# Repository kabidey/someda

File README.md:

# someda

**Describe a circuit. Get a KiCad project you could send to a board house, with every claim checked.**

someda is an electronics design engine written in Rust. You give it a small description of a
circuit: the parts, how they connect, and a bit of intent such as "put the USB connector on
the top edge". It produces a KiCad schematic and board, placed and routed, checked for signal
integrity, stability and heat, verified by KiCad's own rule checks, and exported as Gerbers,
drill files, a bill of materials, a JLCPCB order package and 3D renders.

It never tells you a board is done unless six independent checks agree. When something is
wrong, it tells you what, in plain words, instead of hiding it.

The description can come from you, from a script, or from a language model. The model only
writes intent. The engine owns every coordinate, every trace and every verdict. If a plan has
a problem the engine can fix on its own (a misspelled footprint, a missing decoupling
capacitor), it fixes it and builds again.

MIT license. Made by [SomTronics](https://somtronics.org).

## Two ways to use it

**The desktop app.** `someda-app` is a window. Double-click it and it guides you from "which
language model" to "here are your Gerbers". This is the easiest way in. See
[The desktop app](#the-desktop-app) below.

**The command line.** `someda` is the engine itself. Write a plan file, run one command, read
the result. Scripts, CI pipelines and other programs use this. See [Quick start](#quick-start).

Both come in every release archive.

## What happens in a build

```
plan -> schematic -> footprints -> placement -> routing -> audits -> KiCad checks -> exports -> six gates
```

1. **Schematic.** A readable sheet with real library symbols and labelled pins. KiCad's ERC
   checks it.
2. **Footprints.** Real KiCad library footprints, found by their library name. A misspelled
   name is replaced by the closest footprint in that library, and the engine says so. A part
   the libraries do not have is reported, never guessed.
3. **Placement.** Mounting holes go in their corners. Edge connectors are turned so their
   opening faces the edge, then placed on it. Parts sit next to the pins they share a net
   with. Fine-pitch chips get room for their escape vias. Hot parts keep their distance.
   A connector that finds no room on its edge is moved to the next edge and the board is
   placed again.
4. **Routing.** Two, four or six copper layers on JLCPCB rules. Copper planes on the inner
   layers, with a via for every pad that needs them. Escape vias for every fine-pitch pin.
   Differential pairs are routed first, as coupled pairs at a real cross-section from the
   fab's impedance tables, with matched lengths. Fast nets keep 3W/5W spacing from each
   other. Impedance-controlled traces get the width the stackup calls for and stay over a
   solid plane. When something does not fit, the router rips up and tries again.
5. **Audits on the routed copper.** Stray inductance and capacitance per net. Standing-wave
   ratio and stub resonances. Unterminated transmission lines. Crosstalk measured on the
   actual copper. The loop inductance of every decoupling capacitor as mounted. Regulator
   output capacitance against the datasheet. Crystal loads and trace lengths. Switch-node
   loops. Power delivery impedance per rail. Junction temperatures. Whether JLCPCB can make
   it at all.
6. **KiCad.** ERC, DRC with the zones refilled, Gerbers, drill files and map, position file,
   bill of materials, 3D renders with component bodies.
7. **Exports.** A detailed BOM (quantity, references, value, part number, LCSC number,
   package) and a JLCPCB order package: Gerber zip with Protel names, merged drill file,
   assembly BOM, and a placement file with the rotation corrections JLCPCB expects.
8. **Six gates.** DRC, shorts, unrouted connections, copper pours, Gerbers, drill. All six
   pass and the build says `HONEST-DONE`. Anything else is `NOT DONE`, with the failing gate
   named.

If the plan had something the engine could repair, it repairs it and runs again, up to three
times by default. Each change is printed as a `repair:` line. Anything only you can change
is printed as a `suggest:` line with the exact edit. The plan as it was finally built is
saved next to the outputs as `plan.built.json`.

## The desktop app

Start `someda-app`. It takes you through six screens.

**Language model.** Pick a provider: Anthropic, OpenAI, DeepSeek, Kimi, Mistral, Z.ai,
Ollama Cloud, OpenRouter, NVIDIA NIM, an Ollama running on your own machine, or any other
endpoint that speaks the OpenAI protocol. Paste a key, ask the provider for its model list,
send one test message to be sure it works. The key is saved in your user configuration
folder where only you can read it, and it is handed to the engine through the environment,
never on a command line and never in a log.

**KiCad and libraries.** The app looks for `kicad-cli` and KiCad's footprint, symbol and
3D model libraries. If they are missing it can install KiCad for you: with apt on Debian
and Ubuntu, with the official installer on Windows, from the disk image on macOS.

**What to build.** Say what the board is for, what powers it, what it connects to. The
model may only do two things: ask you a few multiple-choice questions, each with a
recommended answer, about things that change the design; or propose a plan. It does not get
to ask about pinouts, and it does not get to declare the plan finished. The engine does
that. It checks every part against the installed KiCad libraries: does the symbol exist,
does the footprint exist, is every pin number the plan uses really a pin of that symbol.
It shows you the pin table it found, for example `U1: 1 GND, 2 TRIG, 3 OUT, 7 DISCH, 8 VCC`.
A misspelled name is corrected on the spot. When there is a real choice, you get a question
with the real options. When the model used a pin that does not exist, the plan goes back to
the model together with the pin table, and the model tries again. Nothing is built until the
engine is satisfied.

**Build.** Footprints and 3D models the libraries lack are fetched from KiCad's own
repositories. Then the engine runs exactly as it does on the command line, and you watch its
log.

**Result.** The six gates, the 3D render, what the engine repaired, what it suggests, and
the warnings it wants you to read. Buttons open the project folder, the board in KiCad and
the JLCPCB package.

**Change the design.** Describe the change in a sentence. The model proposes a revised plan.
You see the difference, line by line, and confirm. The engine builds the next version. Every
version keeps its plan, its outputs and its build log, so nothing is ever lost.

What has been verified: the whole flow on Linux under a virtual display with the 555
quick-start circuit, against an OpenAI-compatible server, through two versions, all six gates
both times. The Anthropic connection follows the published Messages API but was not tried
against the live service in that environment. The Windows and macOS binaries are built by the
same release workflow; their KiCad install flows have not yet been run on those systems.

## Install

Download the archive for your platform from the
[releases page](https://github.com/kabidey/someda/releases). Each one holds `someda` (the
command line) and `someda-app` (the window). Linux x86_64, macOS on Apple silicon and Intel,
and Windows x86_64 are covered.

To build from source you need stable Rust:

```bash
cargo build --release                                    # the command line, three direct dependencies
cargo build --release --features app --bin someda-app    # the window
```

For the verification and export steps you need [KiCad](https://www.kicad.org/) with
`kicad-cli` on your PATH, along with KiCad's footprint and 3D model libraries. Everything was
developed and verified against KiCad 10.0.6. If `kicad-cli` lives somewhere unusual, point
`SOMEDA_KICAD_CLI` at it. Without KiCad the engine still plans, places, routes and audits; it
simply reports the KiCad steps as skipped.

Using [Claude Code](https://claude.com/claude-code)? The
[someda plugin](https://github.com/kabidey/someda-claude-plugin) writes the plan from a
conversation, fetches missing parts, runs this engine and reports the gates.

## Quick start

`examples/plan_555.json` describes an NE555 blinking an LED, with 5 V arriving on a header at
the left edge and the timer's decoupling capacitor asked to sit next to it:

```json
{
  "name": "555 LED blinker",
  "description": "NE555 astable at about 1 Hz driving an LED",
  "layers": 2,
  "components": [
    {"reference": "U1", "value": "NE555", "lib_id": "Timer:NE555", "footprint": "Package_DIP:DIP-8_W7.62mm", "position": "center"},
    {"reference": "R1", "value": "10k",   "lib_id": "Device:R",   "footprint": "Resistor_SMD:R_0603_1608Metric"},
    {"reference": "R2", "value": "100k",  "lib_id": "Device:R",   "footprint": "Resistor_SMD:R_0603_1608Metric"},
    {"reference": "R3", "value": "330",   "lib_id": "Device:R",   "footprint": "Resistor_SMD:R_0603_1608Metric"},
    {"reference": "C1", "value": "4.7uF", "lib_id": "Device:C",   "footprint": "Capacitor_SMD:C_0805_2012Metric"},
    {"reference": "C2", "value": "100nF", "lib_id": "Device:C",   "footprint": "Capacitor_SMD:C_0603_1608Metric", "near": "U1"},
    {"reference": "D1", "value": "red",   "lib_id": "Device:LED", "footprint": "LED_SMD:LED_0805_2012Metric"},
    {"reference": "J1", "value": "5V in", "lib_id": "Connector:Conn_01x02", "footprint": "Connector_PinHeader_2.54mm:PinHeader_1x02_P2.54mm_Vertical", "position": "left_edge"}
  ],
  "nets": [
    {"name": "VCC", "pins": ["J1:1", "U1:8", "U1:4", "R1:1", "C2:1"]},
    {"name": "GND", "pins": ["J1:2", "U1:1", "C1:2", "C2:2", "D1:1"]},
    {"name": "DIS", "pins": ["U1:7", "R1:2", "R2:1"]},
    {"name": "THR", "pins": ["U1:6", "U1:2", "R2:2", "C1:1"]},
    {"name": "OUT", "pins": ["U1:3", "R3:1"]},
    {"name": "LED", "pins": ["R3:2", "D1:2"]}
  ]
}
```

Build it:

```bash
SOMEDA_PLAN_FILE=examples/plan_555.json SOMEDA_PROJECT_DIR=out someda ai build "555 LED blinker"
```

The engine prints every stage and finishes with the gate table. With someda 0.8.0 and
kicad-cli 10.0.6 this plan places 8 parts on a 43 by 35 mm board, routes all 15
connections, passes KiCad's ERC and DRC with no errors, and clears all six gates. Afterwards
`out/` contains:

```
out/circuit.kicad_sch  circuit.kicad_pcb  circuit.kicad_pro   the KiCad project
out/circuit-erc.rpt    circuit-drc.rpt                         KiCad's reports
out/fab/               Gerbers, drill and map, positions.csv, bom.csv, bom-detailed.csv, bom.md
out/fab/jlcpcb/        jlcpcb-gerbers.zip, jlcpcb-bom.csv, jlcpcb-cpl.csv
out/render/            board-top.png, board-bottom.png, board-iso.png
out/plan.built.json    the plan as it was built, repairs included
```

You can also let a model write the plan from the command line. Set `SOMEDA_API_KEY`,
`SOMEDA_BASE_URL` and `SOMEDA_MODEL` for any endpoint that speaks the OpenAI protocol
(OpenAI, Azure, vLLM, Ollama, LM Studio, llama.cpp and others), then run
`someda ai build "<what you want>"`. `someda ai plan "<what you want>"` prints the plan and
stops.

## What goes in a plan

A plan is intent, never coordinates. The complete reference is the plugin's
[CONTRACT.md](https://github.com/kabidey/someda-claude-plugin/blob/master/skills/someda/references/CONTRACT.md).
In short:

| Field | Meaning |
|---|---|
| `components[].reference`, `value`, `lib_id`, `footprint` | Designator, value (it may carry power, such as `"1W"`), KiCad symbol, KiCad footprint as `Lib:Name` |
| `components[].position` | `top_left` through `bottom_right`, `center`, or an edge: `left_edge`, `right_edge`, `top_edge`, `bottom_edge` |
| `components[].edge_at`, `edge_overhang_mm` | Where along the edge (0 to 1); how far the body front may stick out past the edge, for USB-C shells and the like |
| `components[].near` | Sit next to this part, on the side of the pins they share |
| `components[].rotation` | Optional. Edge connectors need none; the engine turns the opening toward the edge |
| `components[].lcsc`, `mpn` | Part numbers for the BOM, the JLCPCB package and library fetching |
| `nets[].name`, `pins` | Net name and its members as `"REF:PIN"` |
| `nets[].freq_hz`, `role`, `termination` | Highest frequency; `clock`, `highspeed`, `rf`, `power`; `series`, `parallel`, `on-chip` |
| `layers`, `board` | 2, 4 or 6 copper layers; an optional fixed size in mm (otherwise the engine budgets one from the courtyards) |
| `planes[]` | `{net, layer, region, priority}`: a whole layer, a rectangle, or `"auto"` (the owning chip's pins plus 5 mm) |
| `pairs[]` | `{p, n, z_diff, skew_mm}`: differential pairs, routed as coupled pairs |

## What has actually been built with it

Every number here comes from an unedited build log. The complete outputs of the biggest board
are kept as evidence in the plugin repository:
[examples/sompi-v3s/evidence](https://github.com/kabidey/someda-claude-plugin/tree/master/examples/sompi-v3s/evidence).

- **The 555 blinker** above: 15 of 15 connections routed, DRC clean, six gates. The same plan
  with a misspelled footprint and no decoupling capacitor passes the six gates after one
  repair round, in which the engine corrected the name and added a 100 nF capacitor.
- **A 6-layer board around an LQFP-48**, 26 parts: 31 connections and 46 plane fanouts,
  DRC clean, six gates.
- **SomPi-V3s**, a single-board computer around the Allwinner V3s: 132 parts on 90 by 60 mm,
  six layers on JLCPCB's JLC06161H-3313 stackup, USB-C, 10/100 Ethernet, microSD, SPI flash,
  40-pin LCD and 24-pin MIPI camera connectors, an audio jack, a GPIO header, two bucks and
  two LDOs. 187 of 187 connections routed, 225 plane fanouts, 104 escape vias. All seven
  differential pairs coupled within their skew budgets: the two USB pairs at 0.65 mm and
  0.52 mm of the 1.1 mm allowed, one of them through a via crossover; the Ethernet pairs within
  0.01 mm of 0.25; the three MIPI pairs at 0.00 mm of 0.15. No crosstalk violations. KiCad DRC
  clean. Six gates. The engine turned every edge connector to face its edge from the footprint
  alone, moved the audio jack to the bottom edge when the top edge had no slot deep enough,
  and grew the 1.8 V plane island so its capacitors could reach it. The warnings it left are
  real and listed: crystal traces of 11 to 17 mm, one capacitor with a 7.4 nH loop, three
  capacitors beyond the island, a board density of 147 percent.

What "six gates" does not mean: none of these boards has been simulated or manufactured.
Connector pinouts follow common conventions and must be checked against the parts you buy.
3D bodies fetched from LCSC were not compared with physical parts. Skew between pairs (clock
to data) is not enforced. Everything is placed on the top side.

## Environment variables

| Variable | What it does |
|---|---|
| `SOMEDA_PLAN_FILE` | Build this plan instead of asking a model |
| `SOMEDA_PROJECT_DIR` | Where the outputs go (default `./someda-build`) |
| `SOMEDA_FOOTPRINT_DIRS` | Extra `.pretty` folders, searched before KiCad's |
| `SOMEDA_REPAIR_ROUNDS` | Repair rounds after the first build (default 3; 0 turns them off) |
| `SOMEDA_STOP_AFTER` | `schematic` or `route`: write that much and stop, for example to review a schematic first |
| `SOMEDA_KICAD_CLI` | Path to `kicad-cli` |
| `SOMEDA_API_KEY`, `SOMEDA_BASE_URL`, `SOMEDA_MODEL` | The planning model (the `OPENAI_*` names work too) |
| `SOMEDA_ROUTE_DEBUG` (`1` or `2`), `SOMEDA_ROUTE_DEBUG_NET`, `SOMEDA_PLACE_DEBUG` | Router and placer diagnostics: occupancy maps around failed pins, corridor decisions, placement targets |
| `KICAD10_3DMODEL_DIR` (or 9, 8) | Where the 3D bodies for the renders are, when KiCad is installed somewhere unusual |

## Working with existing KiCad files

The engine also reads boards and schematics you already have:

```
someda info       <board.kicad_pcb>          summary of the board
someda drc        <board.kicad_pcb>          design rule checks
someda validate   <board.kicad_pcb>          parse and check (exit 1 on errors)
someda repair     <board.kicad_pcb>          nudge pads inside the outline until the checks pass
someda report     <board.kicad_pcb> [json|md]
someda erc        <schematic.kicad_sch>      electrical rule check
someda netclasses <board.kicad_pcb>          net class summary
```

## Inside the repository

```
src/orchestrator.rs   the pipeline: plan, stages, gates
src/repair.rs         repair rounds and the plan edits they make
src/placer.rs         courtyard placement
src/router.rs         grid router; router/pairs.rs: differential-pair corridors
src/si.rs stability.rs pdn.rs thermal.rs   audits on the routed board
src/formulas.rs materials.rs netfreq.rs    physics, JLCPCB stackups, per-net frequency
src/footprint_lib.rs board.rs sexp.rs      KiCad footprints, board model, s-expressions
src/schematic.rs drc.rs rules.rs           schematic generation and ERC, engine DRC, fab rules
src/kicad_cli.rs bom.rs jlcpcb.rs          kicad-cli steps, BOM, JLCPCB package
src/app/              the desktop app's logic, with no GUI code, all unit-tested
src/bin/someda-app/   the window (egui), behind the "app" feature
examples/             plan_555.json; formula_probe prints every formula; app_e2e drives the app's flow without a window
tests/                a corpus of real boards and fixtures
```

`cargo test` runs about 220 tests. `cargo run --example formula_probe` prints the physics
outputs so you can compare them with independent references. Pushing a `v*` tag builds the
release binaries for all four platforms.

[ARCHITECTURE.md](ARCHITECTURE.md) explains the design and why "done" has to be earned.
[ROADMAP.md](ROADMAP.md) lists the milestones. [CHANGELOG.md](CHANGELOG.md) says what each
version changed and what it was verified against.

## Where it comes from

someda is an original implementation of the ideas documented in the
[SomTronics AI-EDA study](https://github.com/kabidey/somtronics-ai-eda-study) of a commercial
AI-EDA product. It uses the public KiCad file formats, and its rule checks and repair loop
were written from scratch. It contains no code, text or material from the product that was
studied. MIT license.

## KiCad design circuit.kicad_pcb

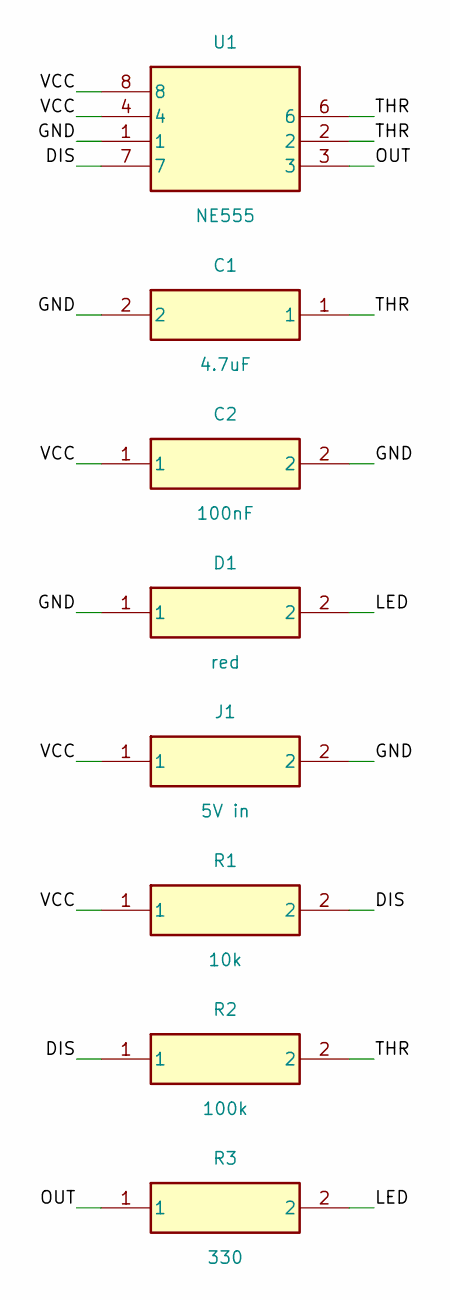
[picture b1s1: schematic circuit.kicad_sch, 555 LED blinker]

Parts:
C1: 4.7uF
C2: 100nF
D1: red
J1: 5V in
R1: 10k
R2: 100k
R3: 330
U1: NE555

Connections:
DIS: R1.2, R2.1, U1.7
GND: C1.2, C2.2, D1.1, J1.2, U1.1
LED: D1.2, R3.2
OUT: R3.1, U1.3
THR: C1.1, R2.2, U1.2, U1.6
VCC: C2.1, J1.1, R1.1, U1.4, U1.8

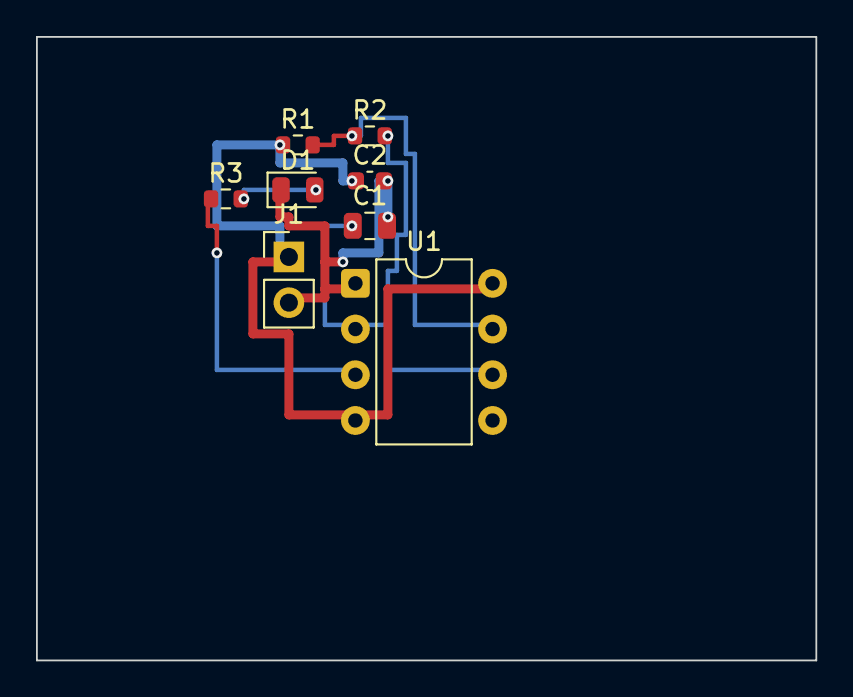
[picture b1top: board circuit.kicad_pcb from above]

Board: 2 copper layers, 43.3 x 34.6 mm, 8 parts (0 on the bottom side), 6 nets.
